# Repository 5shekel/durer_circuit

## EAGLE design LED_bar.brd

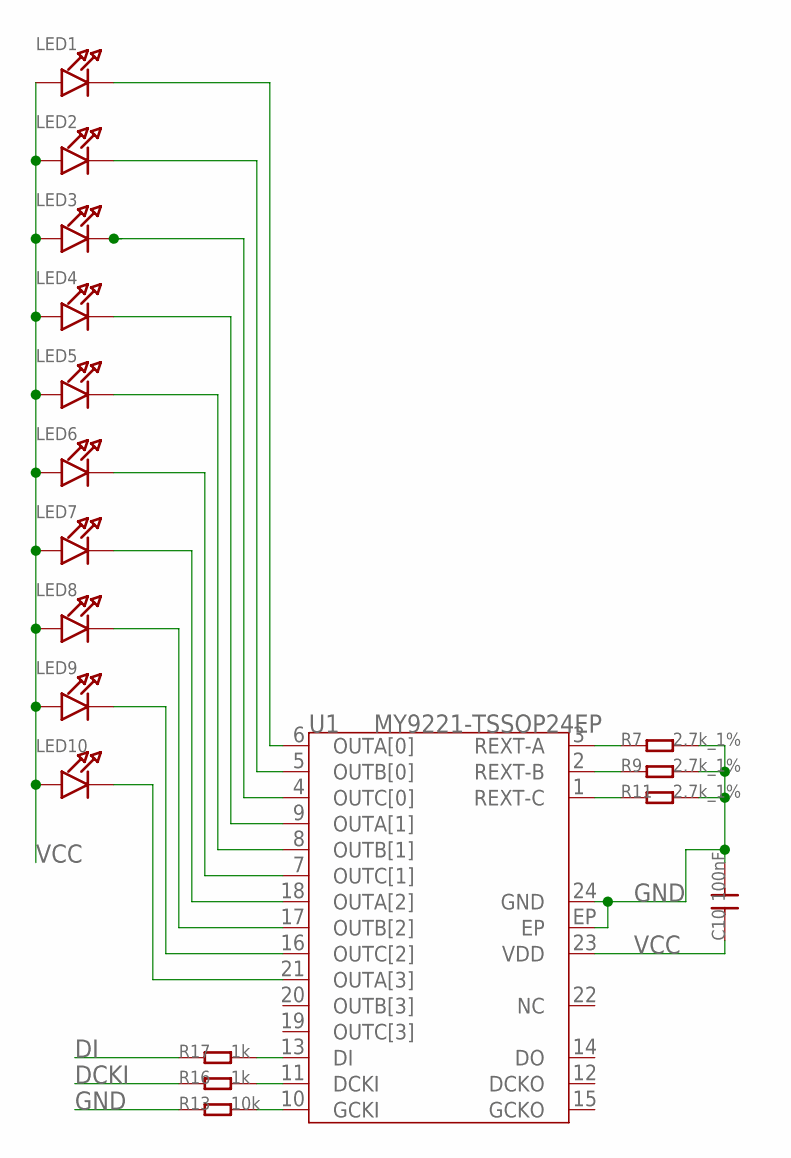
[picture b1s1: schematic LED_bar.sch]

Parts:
C10: 100nF; 0603
LED1, LED2, LED3, LED4, LED5, LED6, LED7, LED8, LED9, LED10: LED0805; CHIPLED_0805
R7, R9, R11: 2.7k_1%; 0603
R13: 10k; 0603
R16, R17: 1k; 0603
U1: MY9221-TSSOP24EP; TSSOP24EP

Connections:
DCKI: R16.1
DI: R17.1
GND: C10.2, R7.2, R9.2, R11.2, R13.1, U1.24 (GND), U1.EP
LED-1: LED1.C, U1.6 (OUTA[0])
LED-2: LED2.C, U1.5 (OUTB[0])
LED-3: LED3.C, U1.4 (OUTC[0])
LED-7: LED7.C, U1.18 (OUTA[2])
LED-8: LED8.C, U1.17 (OUTB[2])
LED-10: LED10.C, U1.21 (OUTA[3])
unnamed: R17.2, U1.13 (DI)
unnamed: R16.2, U1.11 (DCKI)
unnamed: R13.2, U1.10 (GCKI)
unnamed: R11.1, U1.1 (REXT-C)
unnamed: R9.1, U1.2 (REXT-B)
unnamed: R7.1, U1.3 (REXT-A)
unnamed: LED9.C, U1.16 (OUTC[2])
unnamed: LED4.C, U1.9 (OUTA[1])
unnamed: LED5.C, U1.8 (OUTB[1])
unnamed: LED6.C, U1.7 (OUTC[1])
VCC: C10.1, LED1.A, LED2.A, LED3.A, LED4.A, LED5.A, LED6.A, LED7.A, LED8.A, LED9.A, LED10.A, U1.23 (VDD)

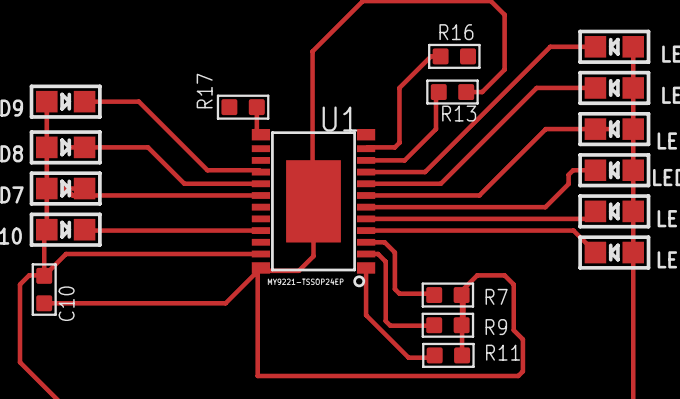
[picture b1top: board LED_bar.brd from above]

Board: 2 copper layers, 18 parts (0 on the bottom side), 18 nets.

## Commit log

2015-01-02 :confetti_ball: Added .gitattributes & .gitignore files
2015-01-02 first commit
    based on led bar eagle files from seeedstudio
    includes PDF file with traces and one with dimensions
2015-01-28 big pic

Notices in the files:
parts and their libraries:
microbuilder: This work is placed in the public domain, and may be freely used for commercial and non-commercial work with the following conditions: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
